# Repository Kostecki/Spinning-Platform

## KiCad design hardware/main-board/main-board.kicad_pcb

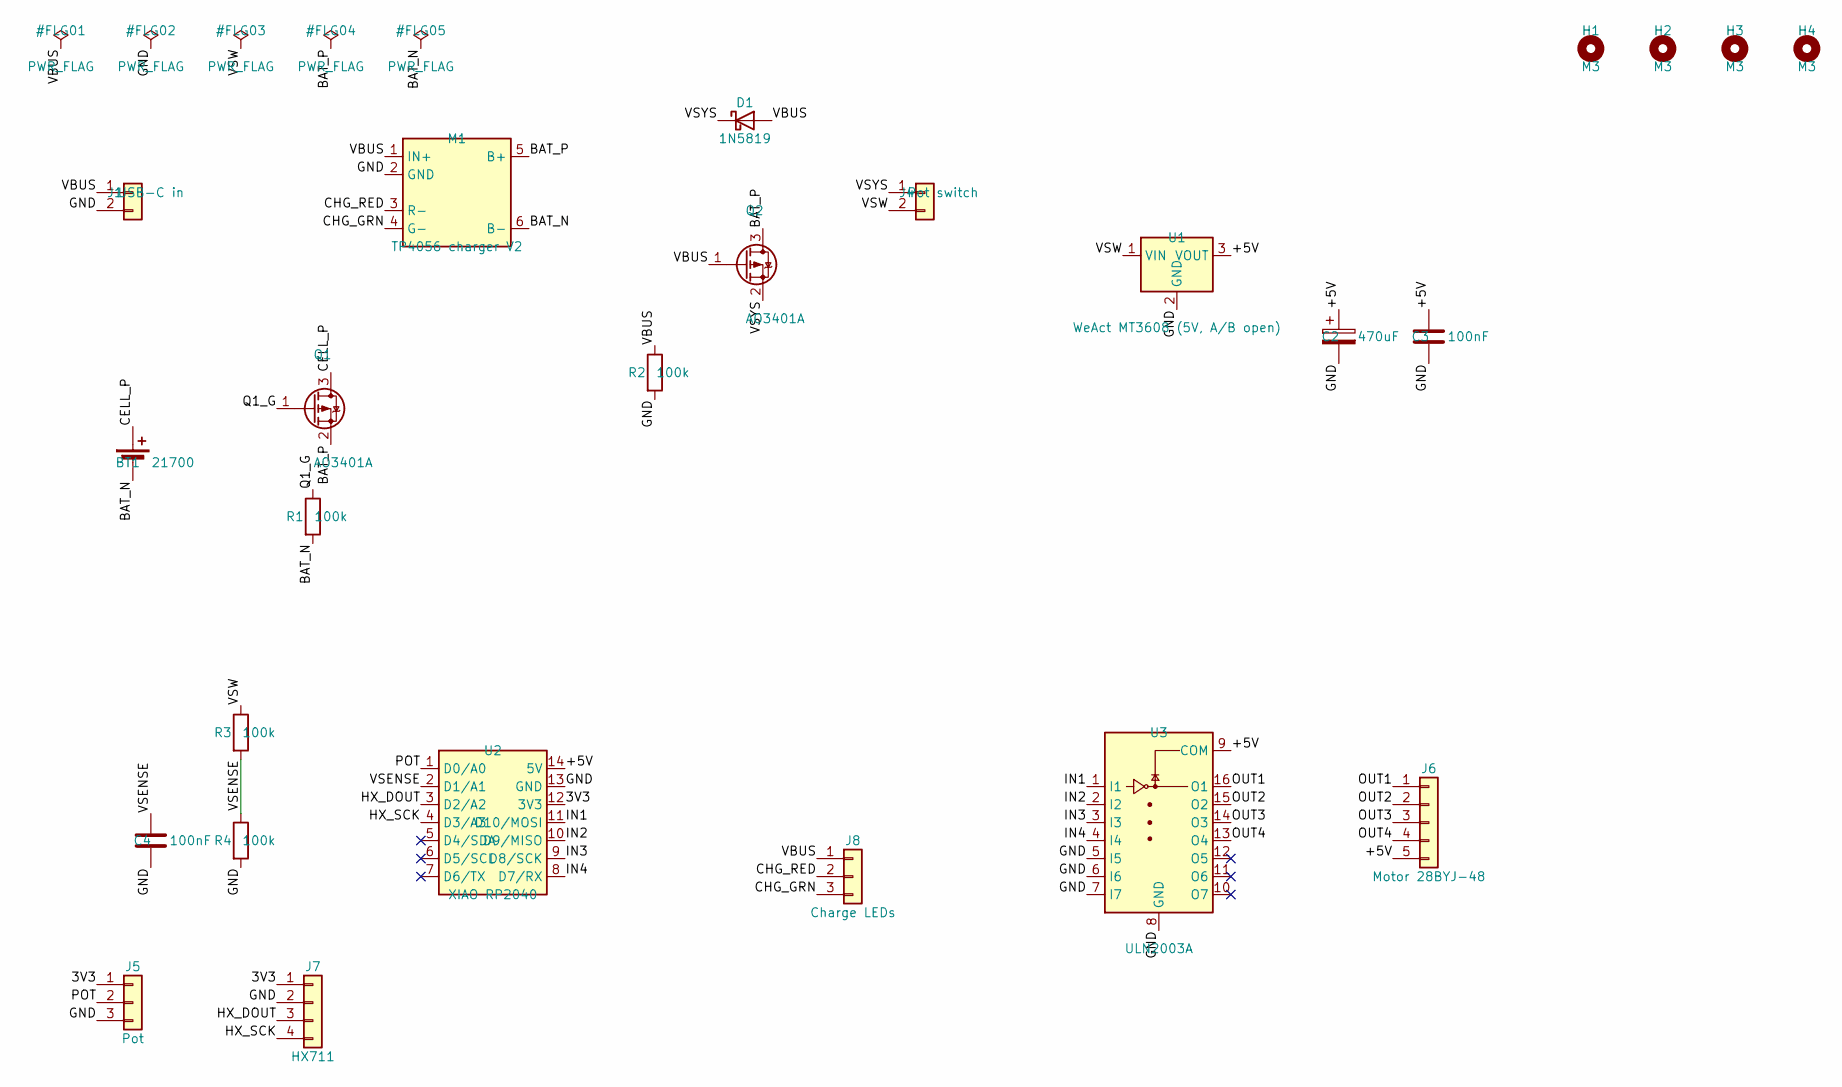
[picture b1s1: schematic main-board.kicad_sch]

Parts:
BT1: 21700; BH-21700-A5BJ001
C2: 470uF; CP_Radial_D6.3mm_P2.50mm
C3, C4: 100nF; C_Disc_D5.0mm_W2.5mm_P5.00mm
D1: 1N5819; D_DO-41_SOD81_P10.16mm_Horizontal
H1, H2, H3, H4: M3; MountingHole_3.2mm_M3
J1: USB-C in; PhoenixContact_MCV_1,5_2-G-3.5_1x02_P3.50mm_Vertical
J4: Pot switch; JST_XH_S2B-XH-A_1x02_P2.50mm_Horizontal
J5: Pot; JST_XH_S3B-XH-A_1x03_P2.50mm_Horizontal
J6: Motor 28BYJ-48; JST_XH_B5B-XH-A_1x05_P2.50mm_Vertical
J7: HX711; PinHeader_1x04_P2.54mm_Vertical
J8: Charge LEDs; PhoenixContact_MCV_1,5_3-G-3.5_1x03_P3.50mm_Vertical
M1: TP4056 charger V2; TP4056_Charger_V2
Q1, Q2: AO3401A; SOT-23_Handsoldering
R1, R2, R3, R4: 100k; R_Axial_DIN0207_L6.3mm_D2.5mm_P7.62mm_Horizontal
U1: WeAct MT3608 (5V, A/B open); WeAct_MT3608
U2: XIAO RP2040; Seeed_XIAO_Socketed
U3: ULN2003A; DIP-16_W7.62mm_Socket

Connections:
/3V3: J5.1, J7.1, U2.12 (3V3)
/+5V: C2.1, C3.1, J6.5, U1.3 (VOUT), U2.14 (5V), U3.9 (COM)
/BAT_N: BT1.2 (-), M1.6 (B-), R1.2
/BAT_P: M1.5 (B+), Q1.2 (S), Q2.3 (D)
/CELL_P: BT1.1 (+), Q1.3 (D)
/CHG_GRN: J8.3, M1.4 (G-)
/CHG_RED: J8.2, M1.3 (R-)
/GND: C2.2, C3.2, C4.2, J1.2, J5.3, J7.2, M1.2 (GND), R2.2, R4.2, U1.2 (GND), U2.13 (GND), U3.5 (I5), U3.6 (I6), U3.7 (I7), U3.8 (GND)
/HX_DOUT: J7.3, U2.3 (D2/A2)
/HX_SCK: J7.4, U2.4 (D3/A3)
/IN1: U2.11 (D10/MOSI), U3.1 (I1)
/IN2: U2.10 (D9/MISO), U3.2 (I2)
/IN3: U2.9 (D8/SCK), U3.3 (I3)
/IN4: U2.8 (D7/RX), U3.4 (I4)
/OUT1: J6.1, U3.16 (O1)
/OUT2: J6.2, U3.15 (O2)
/OUT3: J6.3, U3.14 (O3)
/OUT4: J6.4, U3.13 (O4)
/POT: J5.2, U2.1 (D0/A0)
/Q1_G: Q1.1 (G), R1.1
/VBUS: D1.2 (A), J1.1, J8.1, M1.1 (IN+), Q2.1 (G), R2.1
/VSENSE: C4.1, R3.2, R4.1, U2.2 (D1/A1)
/VSW: J4.2, R3.1, U1.1 (VIN)
/VSYS: D1.1 (K), J4.1, Q2.2 (S)

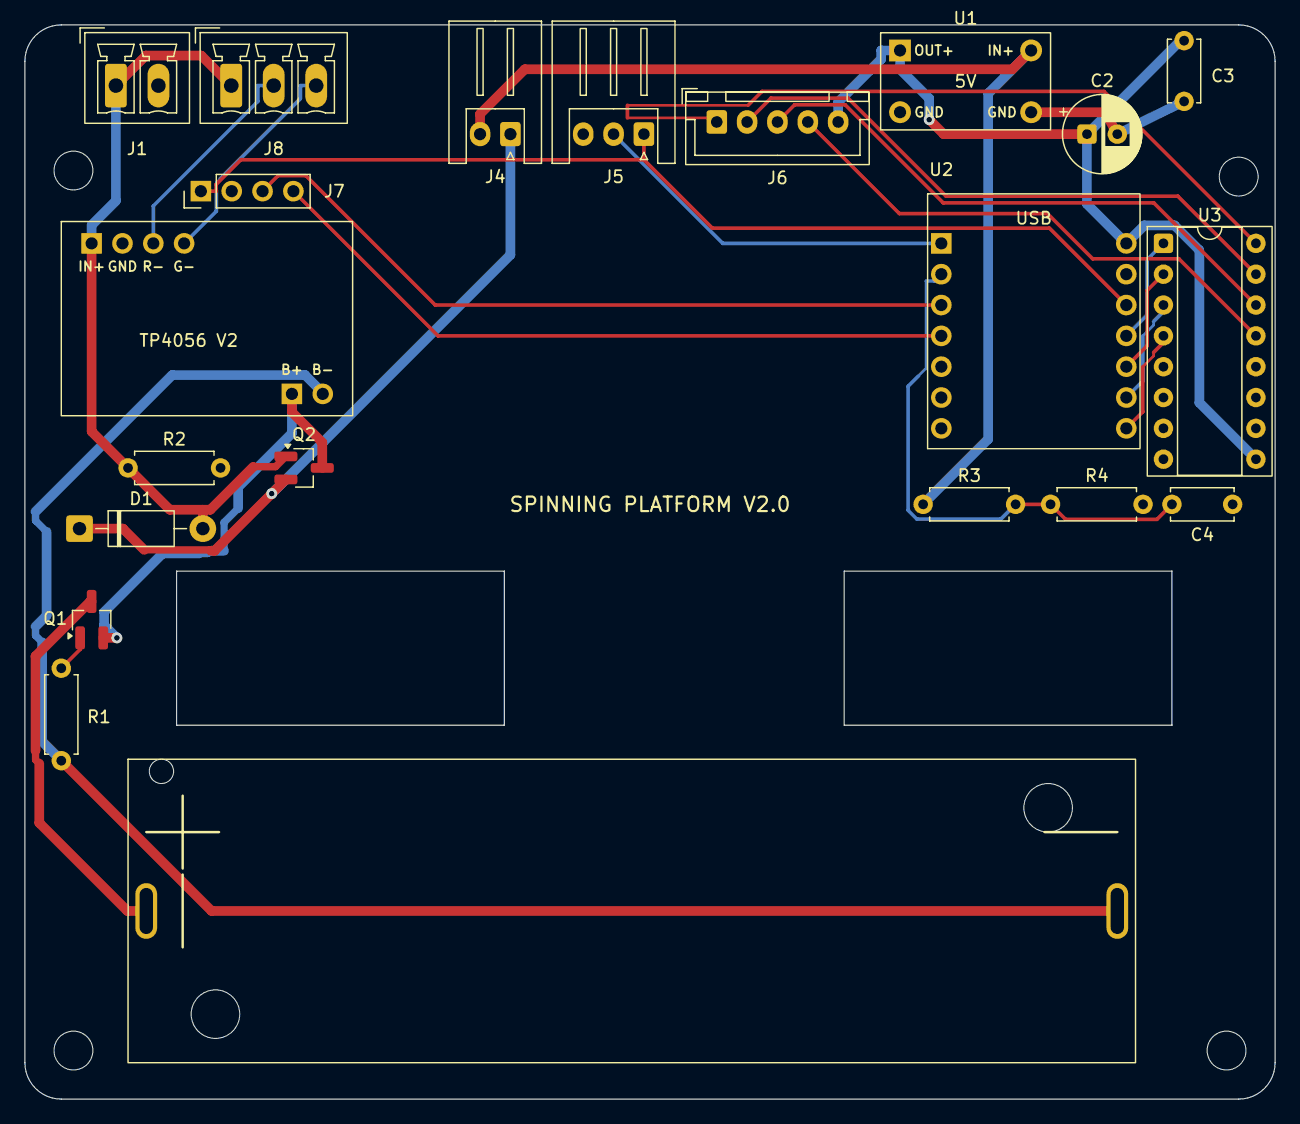
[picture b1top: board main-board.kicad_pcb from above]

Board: 2 copper layers, 103.0 x 88.5 mm, 25 parts (0 on the bottom side), 24 nets.

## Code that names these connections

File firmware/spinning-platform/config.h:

#pragma once

// ---- Pins (XIAO) ----
// Motor: ULN2003 IN1..IN4. Same wiring as V1.
const uint8_t PIN_IN1 = D10;
const uint8_t PIN_IN2 = D9;
const uint8_t PIN_IN3 = D8;
const uint8_t PIN_IN4 = D7;

const uint8_t PIN_POT = A0;         // pot wiper (pot on 3V3)
const uint8_t PIN_VBAT = A1;        // switched supply (battery, or ~4.7 V on USB) via 100k/100k
const uint8_t PIN_HX_DOUT = D2;     // HX711 breakout, powered from 3V3
const uint8_t PIN_HX_SCK = D3;

// Set to 0 when no battery divider is wired (e.g. the V1 board test rig).
#define BATTERY_SENSE 1

// ---- Motor ----
const bool HALF_STEP = false;       // false = two-phase full step (max torque, as V1)
const bool REVERSE = false;
const float STEPS_PER_REV_FULL = 2048.0f;
const float MIN_RPM = 2.0f;
const float MAX_RPM = 15.0f;
const float ACCEL_RPM_PER_S = 8.0f; // ramp so a heavy bottle doesn't slip
const float START_RPM = 1.0f;       // ramp starts/ends here

// ---- Pot ----
const int POT_LOW = 80;             // 12-bit; below this = MIN_RPM
const int POT_HIGH = 4095;

// ---- Scale ----
// Default until calibrated over serial ("c <grams>"). Sign depends on cell orientation.
const float DEFAULT_COUNTS_PER_GRAM = 860.0f;  // 5 kg cell, 2 mV/V, 3V3 excitation
const float ON_GRAMS = 5.0f;                 // something there if above this...
const uint32_t ON_DEBOUNCE_MS = 500;         // ...for this long
const float OFF_GRAMS = 3.0f;                // empty if below this...
const uint32_t OFF_DEBOUNCE_MS = 3000;       // ...for this long
const float NEGATIVE_RETARE_GRAMS = -5.0f;   // reading this far below zero = tare is stale
const uint32_t NEGATIVE_RETARE_MS = 2000;
const float STABLE_BAND_GRAMS = 1.5f;        // auto-zero only when this steady
const uint32_t AUTOZERO_AFTER_IDLE_MS = 5000;
const float AUTOZERO_RATE = 0.1f;            // fraction of error removed per sample
const float SAVE_TARE_DELTA_GRAMS = 0.5f;
const uint32_t SAVE_TARE_MIN_INTERVAL_MS = 10UL * 60 * 1000;

// ---- Battery ----
const float VBAT_DIVIDER = 2.0f;
const float VBAT_LOW = 3.3f;                 // stop below this (under load)...
const uint32_t VBAT_LOW_MS = 10000;          // ...for this long
const float VBAT_RECOVER = 3.6f;             // resume above this (e.g. charging)
